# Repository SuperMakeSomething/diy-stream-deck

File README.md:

# DIY Stream Deck
by: Alex - Super Make Something

date: November 9, 2020

license: Creative Commons - Attribution - Non-Commercial.  More information available at: http://creativecommons.org/licenses/by-nc/3.0/

Arduino code, icon templates, and programming instructions for the DIY Stream Deck featured in Super Make Something Episode 22!

The project video can be found [here](https://youtu.be/_NqYtvLnY5k)!

If you like projects like these, consider subscribing to the Super Make Something YouTube page [here](https://www.youtube.com/supermakesomething?sub_confirmation=1) for more cool builds!  To support more projects like this please consider becoming a [Patron](https://www.patreon.com/SuperMakeSomething).

## Introduction
Arguably one of the best streaming tools besides a camera, microphone, and lights is a Stream Deck, a macro keyboard with an LCD screen behind the buttons, which allows users to program custom shortcuts to control their streaming software and various other applications.  Unfortunately this surge in interest has made these devices either difficult to find or very expensive.  Because of this, I decided to create an open source version, which will hopefully make it easier for those interesting in streaming to go live online, and to make it possible for individuals to create the custom Stream Deck that best suits their streaming needs.

This repository contains code and icon templates required to build your own DIY Stream Deck.  Information found in this repository accompanies the "DIY Stream Deck" build video on the Super Make Something YouTube page, which can be found here.

## Installation instructions and required libraries
Write-up coming soon!  In the meantime, please check out the project video [here](https://youtu.be/_NqYtvLnY5k) for step-by-step instructions about how to build this project.

## Bill of materials
- PCBs: https://bit.ly/2JKsyOw
- 3D Printed Files: https://www.thingiverse.com/thing:4650060
- 3.5in TFT LCD Screen: https://amzn.to/3ke75tS
- Arduino Pro Micro: https://amzn.to/35e6Vys
- Arduino Nano: https://amzn.to/3eHZF0K
- SD Card Breakout Board: https://amzn.to/3kb2Orj
- 6mm Push-Buttons: https://amzn.to/2Ilm4VO
- Rotary Encoder with Push-Button: https://amzn.to/35j7Xtf
- Male/Female Header Kit: https://amzn.to/35ezw6T
- Ribbon Cable: https://amzn.to/2GPOrLq
- 4GB Micro SD Card: https://amzn.to/35eC2tS
- M2 Screw Kit: https://amzn.to/2GKlz77
- M3 Screw Kit: https://amzn.to/2GNitiQ
- Hatchbox Black PLA: https://amzn.to/35fGM2h
- Hatchbox White PLA: https://amzn.to/2InWG1n
- Color Changing PLA: https://amzn.to/35fNuoM
- Resistor Kit (Optional): https://amzn.to/2UcVQY2
- Slow Flash RGB LEDs (Optional): https://amzn.to/2Uep7l2
- 20x20mm Acrylic Squares: https://litko.net/

(All Amazon links are affiliate links.)

## Conclusion
Hopefully you found this project useful!  If you enjoyed this tutorial, consider subscribing to Super Make Something on YouTube [here](https://www.youtube.com/supermakesomething?sub_confirmation=1) for more cool builds!  If you _really_ liked this tutorial and want to support future projects, you can become a [patron on Patreon](https://www.patreon.com/SuperMakeSomething).

If you have any questions or comments, I can most easily be reached on [Twitter](https://twitter.com/supermakesmthng) or [Instagram](https://www.instagram.com/supermakesomething/).  For items or issues specifically related to this project, please leaving your questions in the comments of the accompanying YouTube video so that they can be referenced by others during their own builds.

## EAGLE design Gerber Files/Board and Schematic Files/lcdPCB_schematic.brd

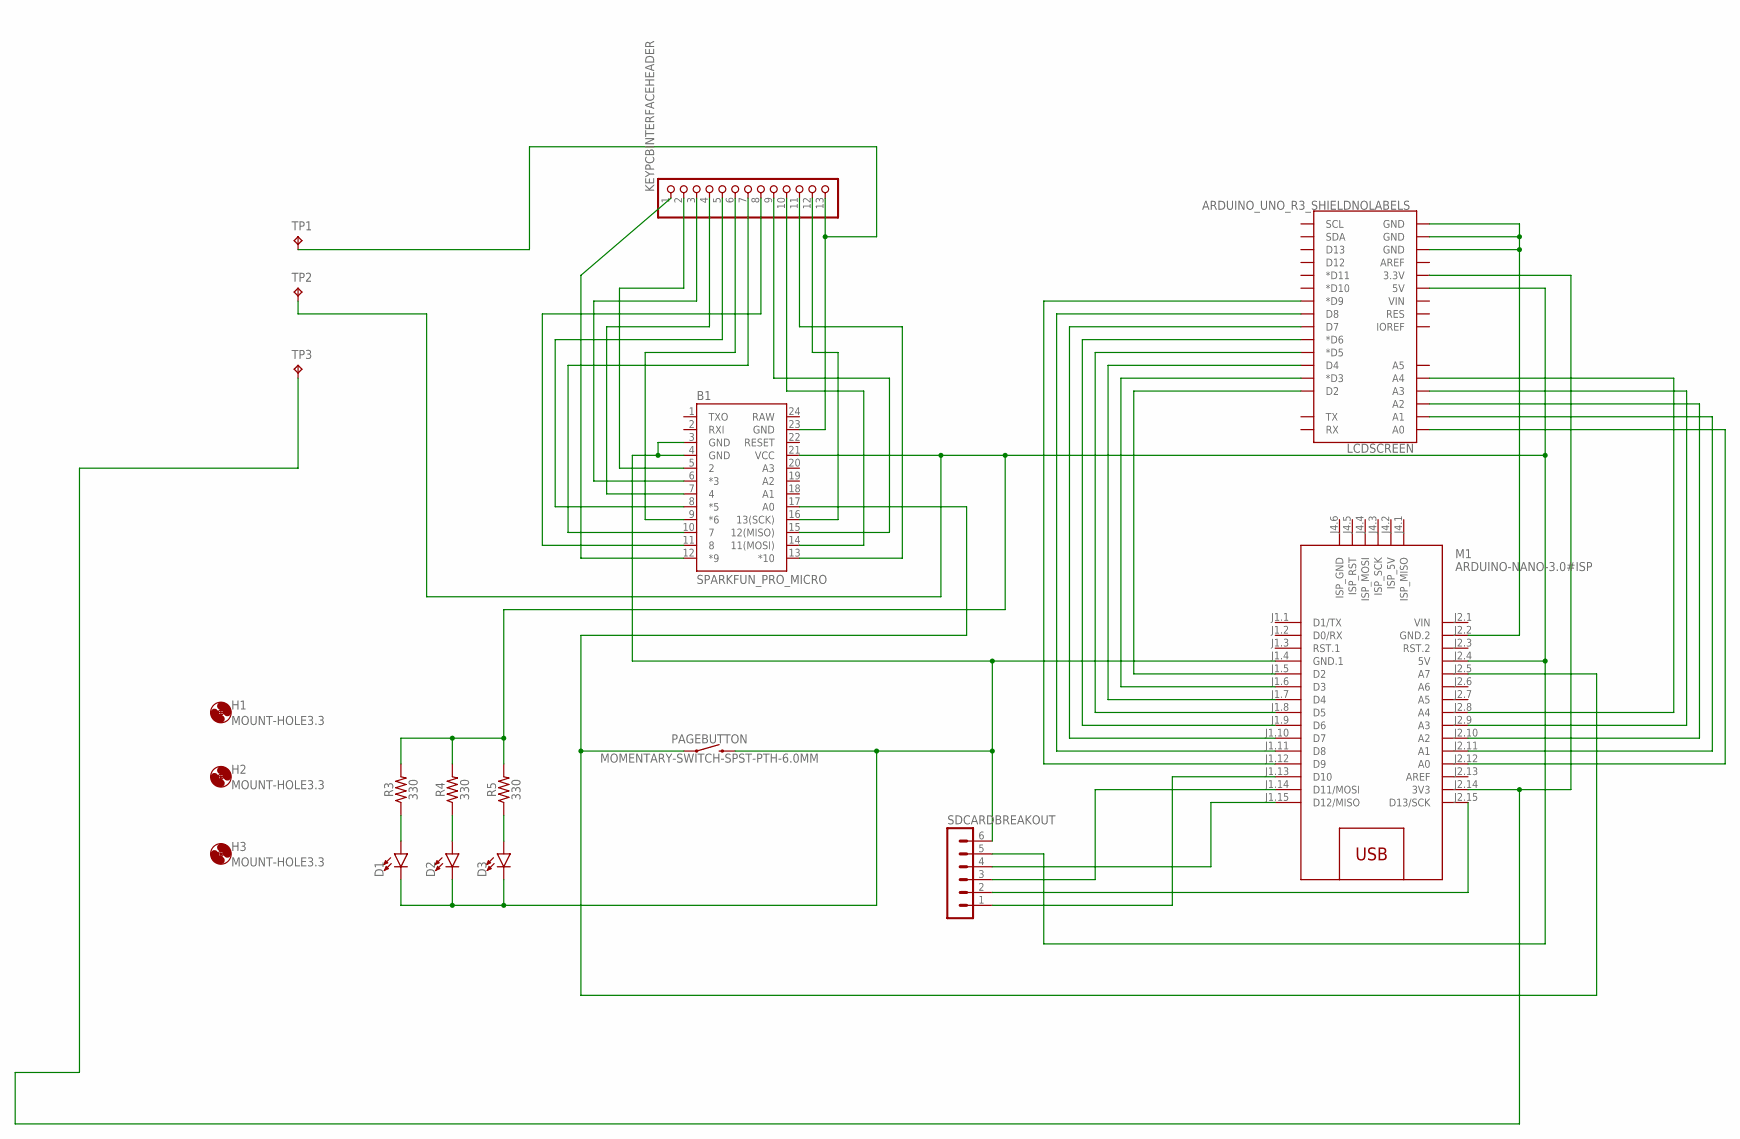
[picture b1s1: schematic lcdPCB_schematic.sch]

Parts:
B1: SPARKFUN_PRO_MICRO
D1, D2, D3: LED-3MM-NO_SILK; LED_3MM-NS
H1, H2, H3: MOUNT-HOLE3.3; 3,3
KEYPCBINTERFACEHEADER: PINHD-1X13; 1X13
LCDSCREEN: ARDUINO_UNO_R3_SHIELDNOLABELS; UNO_R3_SHIELD_NOLABELS
M1: ARDUINO-NANO-3.0#ISP
PAGEBUTTON: MOMENTARY-SWITCH-SPST-PTH-6.0MM; TACTILE_SWITCH_PTH_6.0MM
R3, R4, R5: 330; AXIAL-0.3
SDCARDBREAKOUT: MA06-1
TP1, TP2, TP3: TPTP20SQ; TP20SQ

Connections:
unnamed: LCDSCREEN.A0, M1.J2.12 (A0)
unnamed: LCDSCREEN.A1, M1.J2.11 (A1)
unnamed: LCDSCREEN.A2, M1.J2.10 (A2)
unnamed: LCDSCREEN.A3, M1.J2.9 (A3)
unnamed: LCDSCREEN.A4, M1.J2.8 (A4)
unnamed: LCDSCREEN.D2, M1.J1.5 (D2)
unnamed: LCDSCREEN.D3 (*D3), M1.J1.6 (D3)
unnamed: LCDSCREEN.D4, M1.J1.7 (D4)
unnamed: LCDSCREEN.D5 (*D5), M1.J1.8 (D5)
unnamed: LCDSCREEN.D6 (*D6), M1.J1.9 (D6)
unnamed: LCDSCREEN.D7, M1.J1.10 (D7)
unnamed: LCDSCREEN.D8, M1.J1.11 (D8)
unnamed: LCDSCREEN.D9 (*D9), M1.J1.12 (D9)
unnamed: M1.J1.13 (D10), SDCARDBREAKOUT.1
unnamed: M1.J2.15 (D13/SCK), SDCARDBREAKOUT.2
unnamed: M1.J1.14 (D11/MOSI), SDCARDBREAKOUT.3
unnamed: M1.J1.15 (D12/MISO), SDCARDBREAKOUT.4
unnamed: B1.3 (GND), B1.4 (GND), D1.K (C), D2.K (C), D3.K (C), M1.J1.4 (GND.1), PAGEBUTTON.3 (2), SDCARDBREAKOUT.6
unnamed: B1.21 (VCC), LCDSCREEN.5V, M1.J2.4 (5V), R3.P$2 (2), R4.P$2 (2), R5.P$2 (2), SDCARDBREAKOUT.5, TP2.TP
unnamed: LCDSCREEN.3.3V, M1.J2.14 (3V3), TP3.TP
unnamed: LCDSCREEN.GND@0 (GND), LCDSCREEN.GND@1 (GND), LCDSCREEN.GND@2 (GND), M1.J2.2 (GND.2)
unnamed: B1.12 (*9), KEYPCBINTERFACEHEADER.1
unnamed: B1.5 (2), KEYPCBINTERFACEHEADER.2
unnamed: B1.6 (*3), KEYPCBINTERFACEHEADER.3
unnamed: B1.7 (4), KEYPCBINTERFACEHEADER.4
unnamed: B1.8 (*5), KEYPCBINTERFACEHEADER.5
unnamed: B1.9 (*6), KEYPCBINTERFACEHEADER.6
unnamed: B1.10 (7), KEYPCBINTERFACEHEADER.7
unnamed: B1.11 (8), KEYPCBINTERFACEHEADER.8
unnamed: B1.13 (*10), KEYPCBINTERFACEHEADER.11
unnamed: B1.15 (12(MISO)), KEYPCBINTERFACEHEADER.9
unnamed: B1.14 (11(MOSI)), KEYPCBINTERFACEHEADER.10
unnamed: B1.16 (13(SCK)), KEYPCBINTERFACEHEADER.12
unnamed: B1.17 (A0), M1.J2.5 (A7), PAGEBUTTON.1
unnamed: B1.23 (GND), KEYPCBINTERFACEHEADER.13, TP1.TP
unnamed: D1.A, R3.P$1 (1)
unnamed: D2.A, R4.P$1 (1)
unnamed: D3.A, R5.P$1 (1)
RAW: B1.24 (RAW)
VIN: M1.J2.1 (VIN)

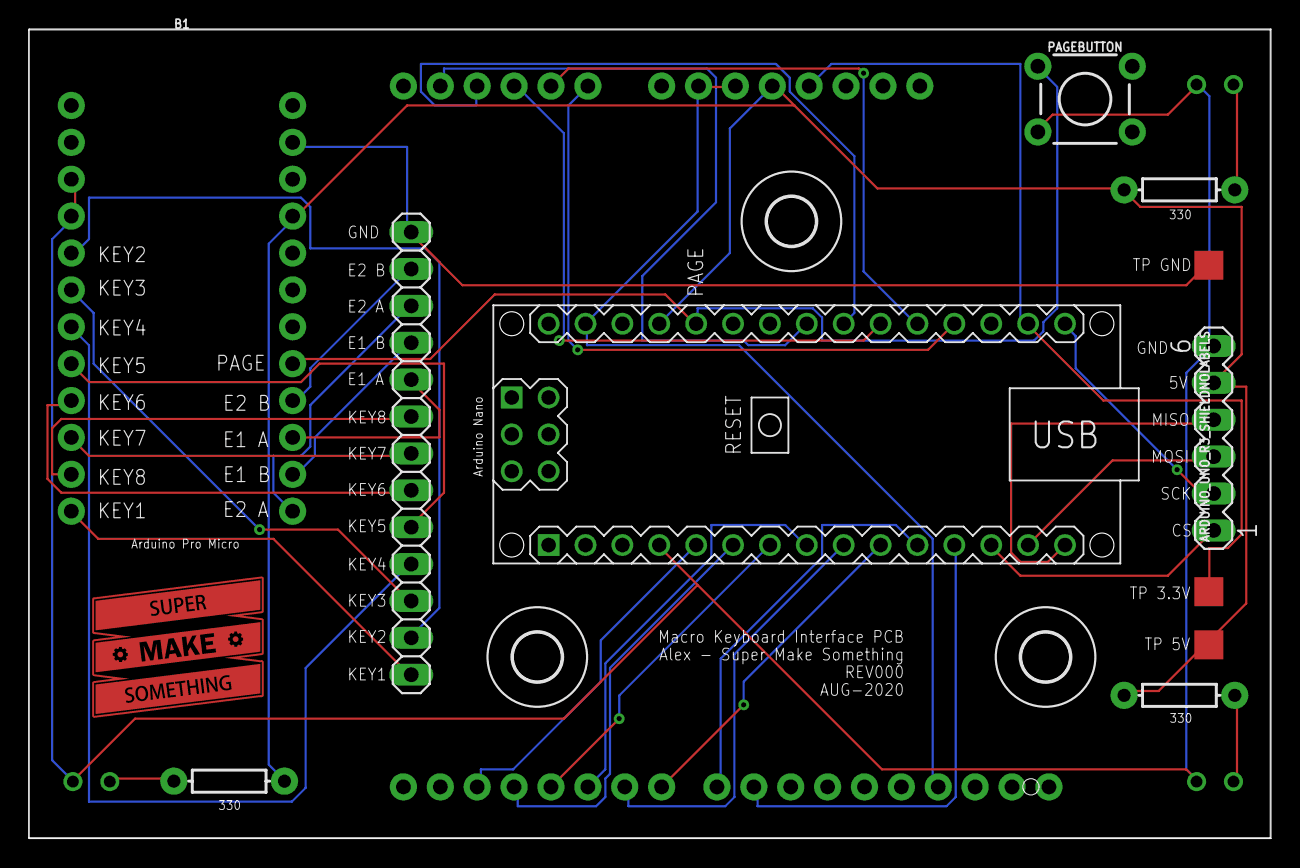
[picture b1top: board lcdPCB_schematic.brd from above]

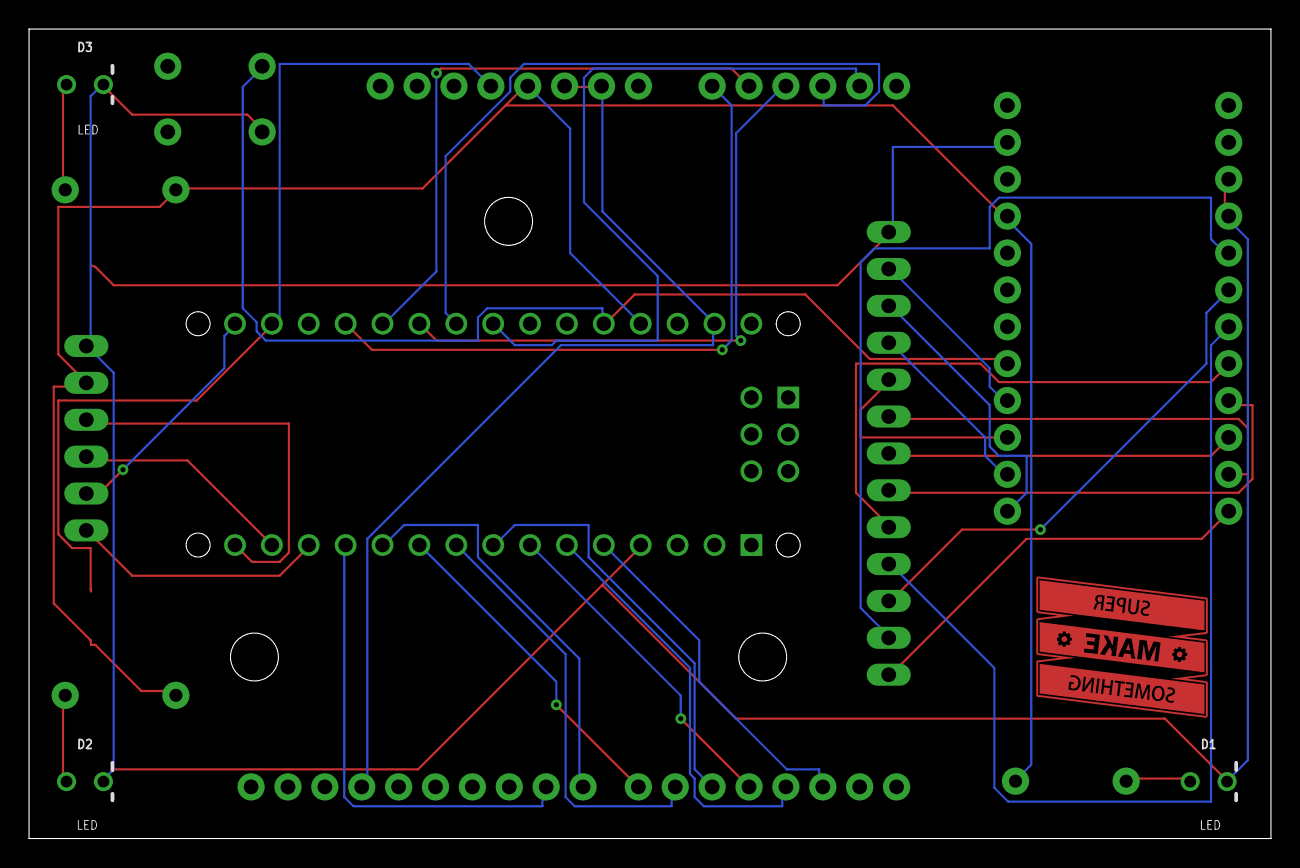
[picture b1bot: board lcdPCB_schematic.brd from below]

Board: 2 copper layers, 85.5 x 55.7 mm, 18 parts (3 on the bottom side), 38 nets.

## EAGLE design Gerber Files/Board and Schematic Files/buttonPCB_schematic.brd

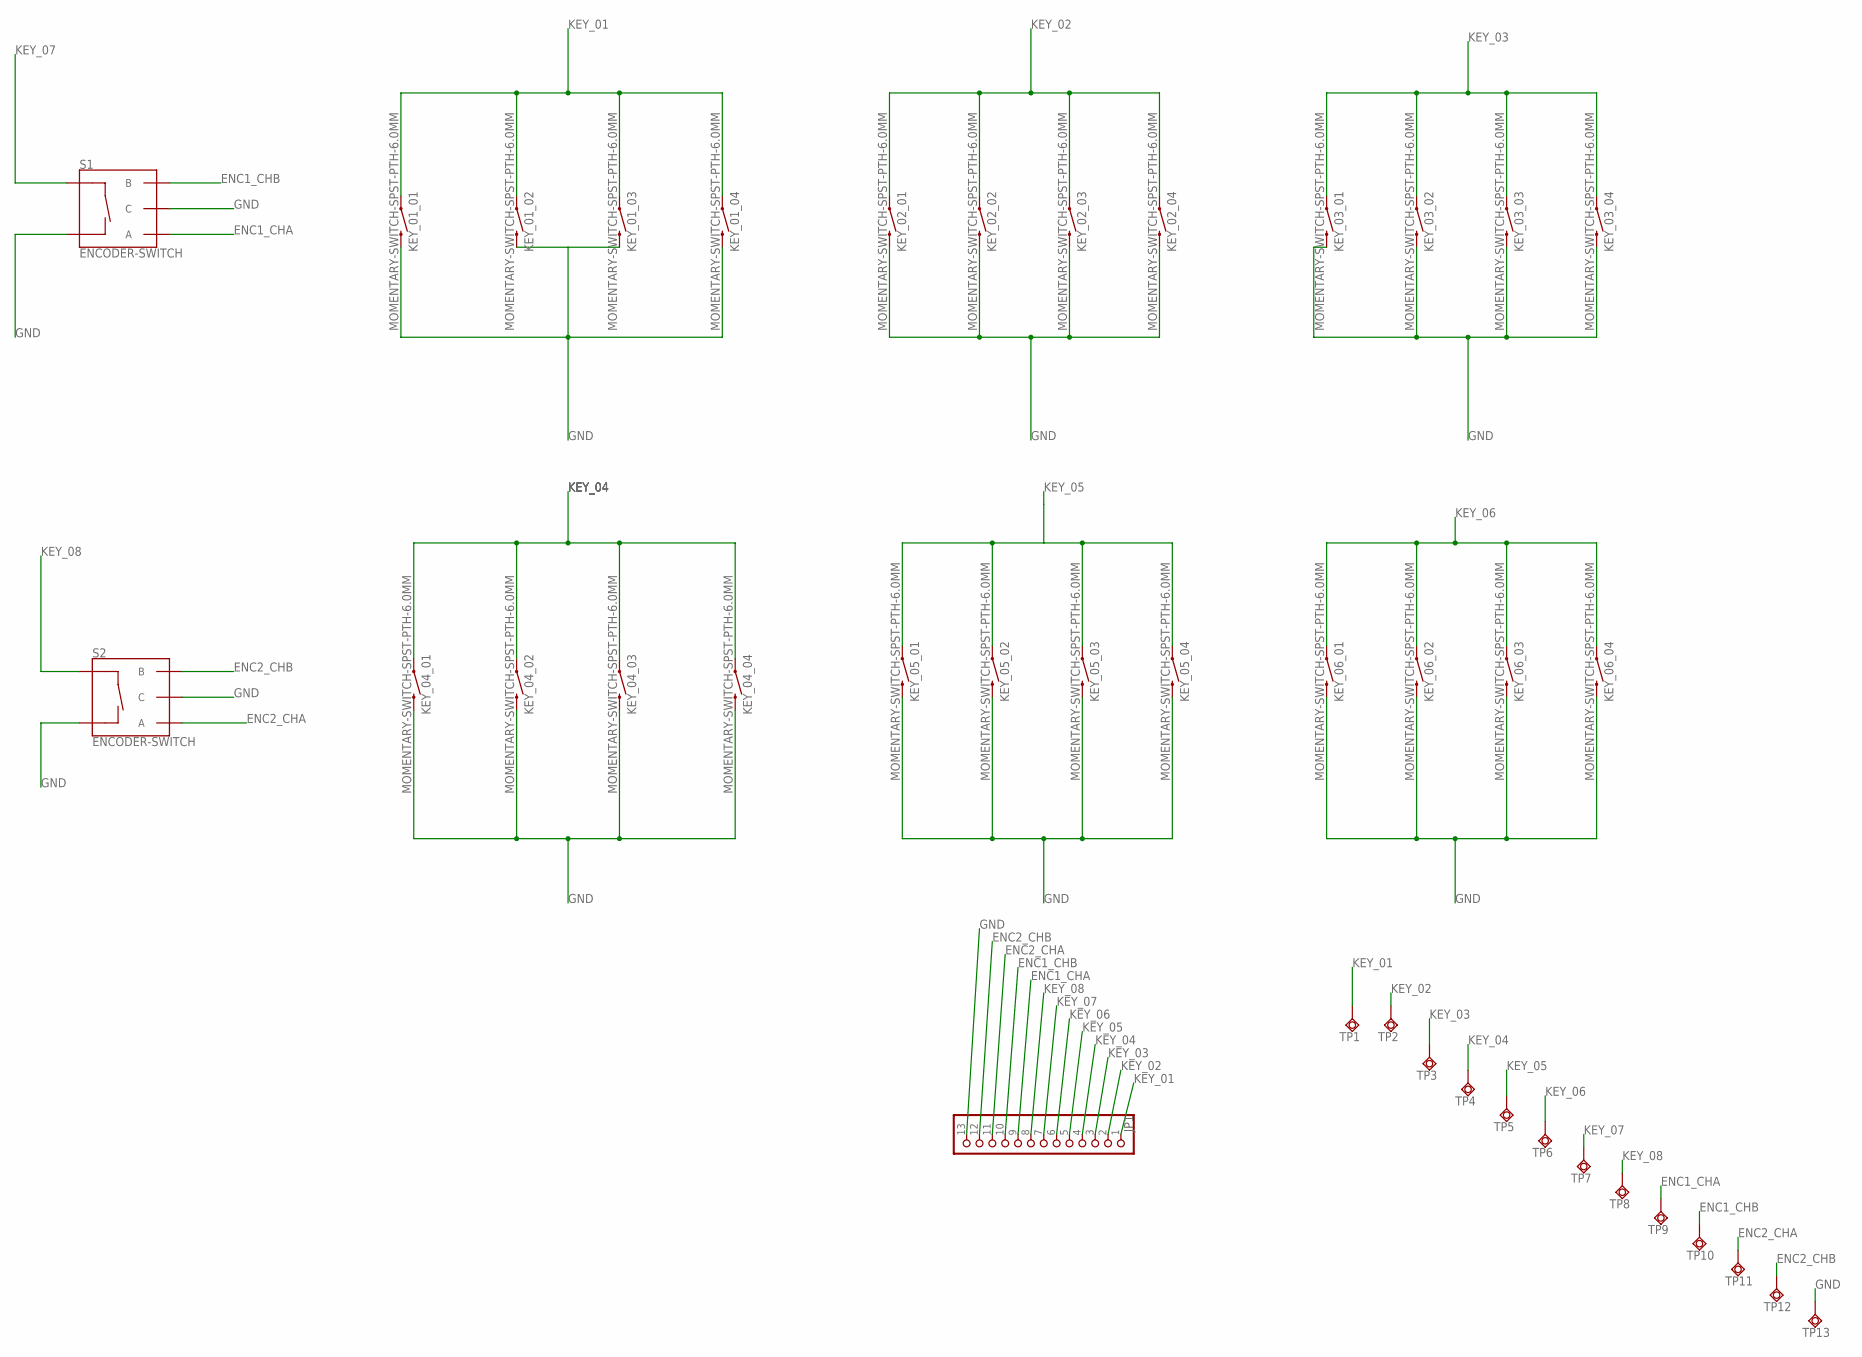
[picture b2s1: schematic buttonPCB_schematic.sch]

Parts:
JP1: PINHD-1X13; 1X13
KEY_01_01, KEY_01_02, KEY_01_03, KEY_01_04, KEY_02_01, KEY_02_02, KEY_02_03, KEY_02_04, KEY_03_01, KEY_03_02, KEY_03_03, KEY_03_04, KEY_04_01, KEY_04_02, KEY_04_03, KEY_04_04, KEY_05_01, KEY_05_02, KEY_05_03, KEY_05_04, KEY_06_01, KEY_06_02, KEY_06_03, KEY_06_04: MOMENTARY-SWITCH-SPST-PTH-6.0MM; TACTILE_SWITCH_PTH_6.0MM
S1, S2: ENCODER-SWITCH; ROTARY_ENC_PLAIN
TP1, TP2, TP3, TP4, TP5, TP6, TP7, TP8, TP9, TP10, TP11, TP12, TP13: TPSQTP18SQ; TP18SQ

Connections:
ENC1_CHA: JP1.9, S1.A, TP9.TP
ENC1_CHB: JP1.10, S1.B, TP10.TP
ENC2_CHA: JP1.11, S2.A, TP11.TP
ENC2_CHB: JP1.12, S2.B, TP12.TP
GND: JP1.13, KEY_01_01.3 (2), KEY_01_02.3 (2), KEY_01_03.3 (2), KEY_01_04.3 (2), KEY_02_01.3 (2), KEY_02_02.3 (2), KEY_02_03.3 (2), KEY_02_04.3 (2), KEY_03_01.3 (2), KEY_03_02.3 (2), KEY_03_03.3 (2), KEY_03_04.3 (2), KEY_04_01.3 (2), KEY_04_02.3 (2), KEY_04_03.3 (2), KEY_04_04.3 (2), KEY_05_01.3 (2), KEY_05_02.3 (2), KEY_05_03.3 (2), KEY_05_04.3 (2), KEY_06_01.3 (2), KEY_06_02.3 (2), KEY_06_03.3 (2), KEY_06_04.3 (2), S1.C, S1.SW-, S2.C, S2.SW-, TP13.TP
KEY_01: JP1.1, KEY_01_01.1, KEY_01_02.1, KEY_01_03.1, KEY_01_04.1, TP1.TP
KEY_02: JP1.2, KEY_02_01.1, KEY_02_02.1, KEY_02_03.1, KEY_02_04.1, TP2.TP
KEY_03: JP1.3, KEY_03_01.1, KEY_03_02.1, KEY_03_03.1, KEY_03_04.1, TP3.TP
KEY_04: JP1.4, KEY_04_01.1, KEY_04_02.1, KEY_04_03.1, KEY_04_04.1, TP4.TP
KEY_05: JP1.5, KEY_05_01.1, KEY_05_02.1, KEY_05_03.1, KEY_05_04.1, TP5.TP
KEY_06: JP1.6, KEY_06_01.1, KEY_06_02.1, KEY_06_03.1, KEY_06_04.1, TP6.TP
KEY_07: JP1.7, S1.SW+, TP7.TP
KEY_08: JP1.8, S2.SW+, TP8.TP

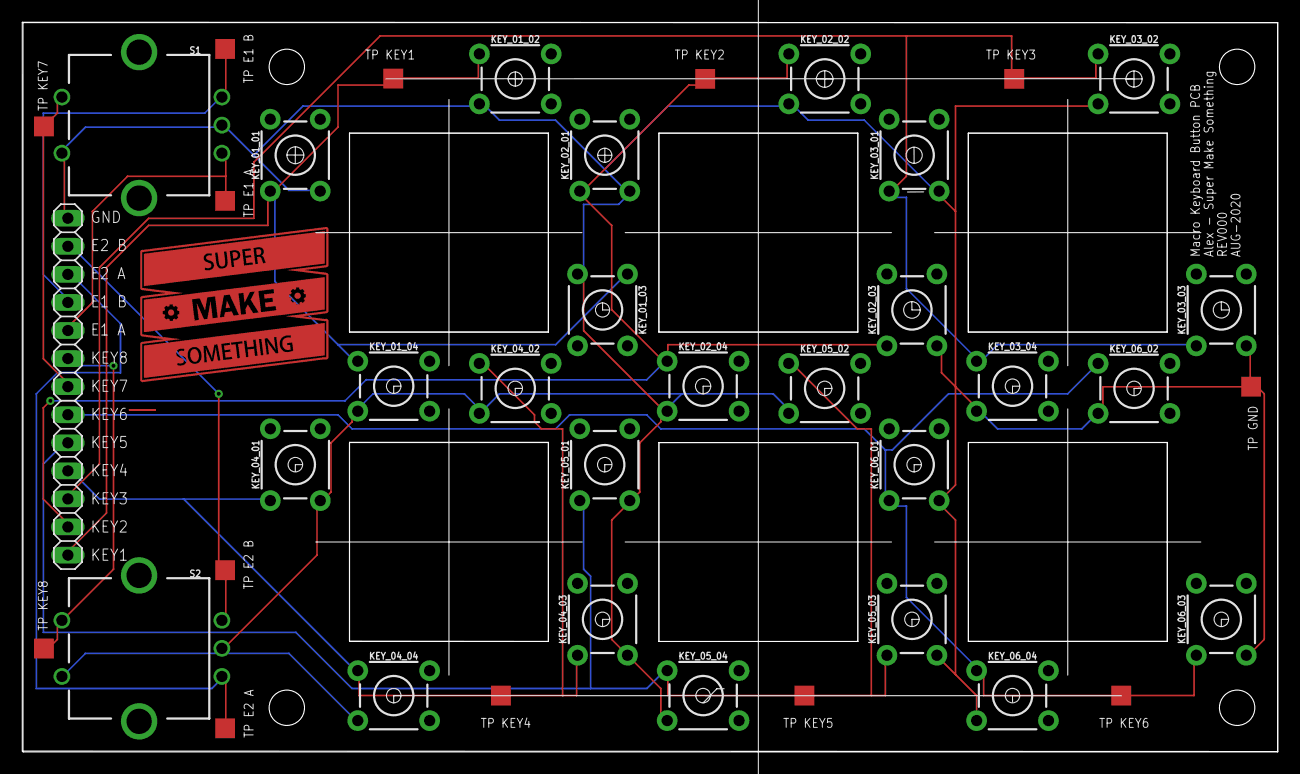
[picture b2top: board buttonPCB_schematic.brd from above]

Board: 2 copper layers, 113.6 x 66.0 mm, 40 parts (0 on the bottom side), 13 nets.

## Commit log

2020-11-09 Added banner image file
2020-11-09 Update README with banner
2020-11-09 Added license information to README
2020-11-09 README formatting
2020-11-09 Added Gerber files
2020-11-11 Added board and schematic files
2020-11-11 Added BoM and link to video
2020-11-11 Additional README formatting
2020-11-11 Added link to STL files
2020-12-12 Added STL and STEP files

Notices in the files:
parts and their libraries:
SparkFun-Switches: Licensing: Creative Commons ShareAlike 4.0 International - https://creativecommons.org/licenses/by-sa/4.0
diy-modules: Released under the Creative Commons Attribution 4.0 International License: http://creativecommons.org/licenses/by/4.0
